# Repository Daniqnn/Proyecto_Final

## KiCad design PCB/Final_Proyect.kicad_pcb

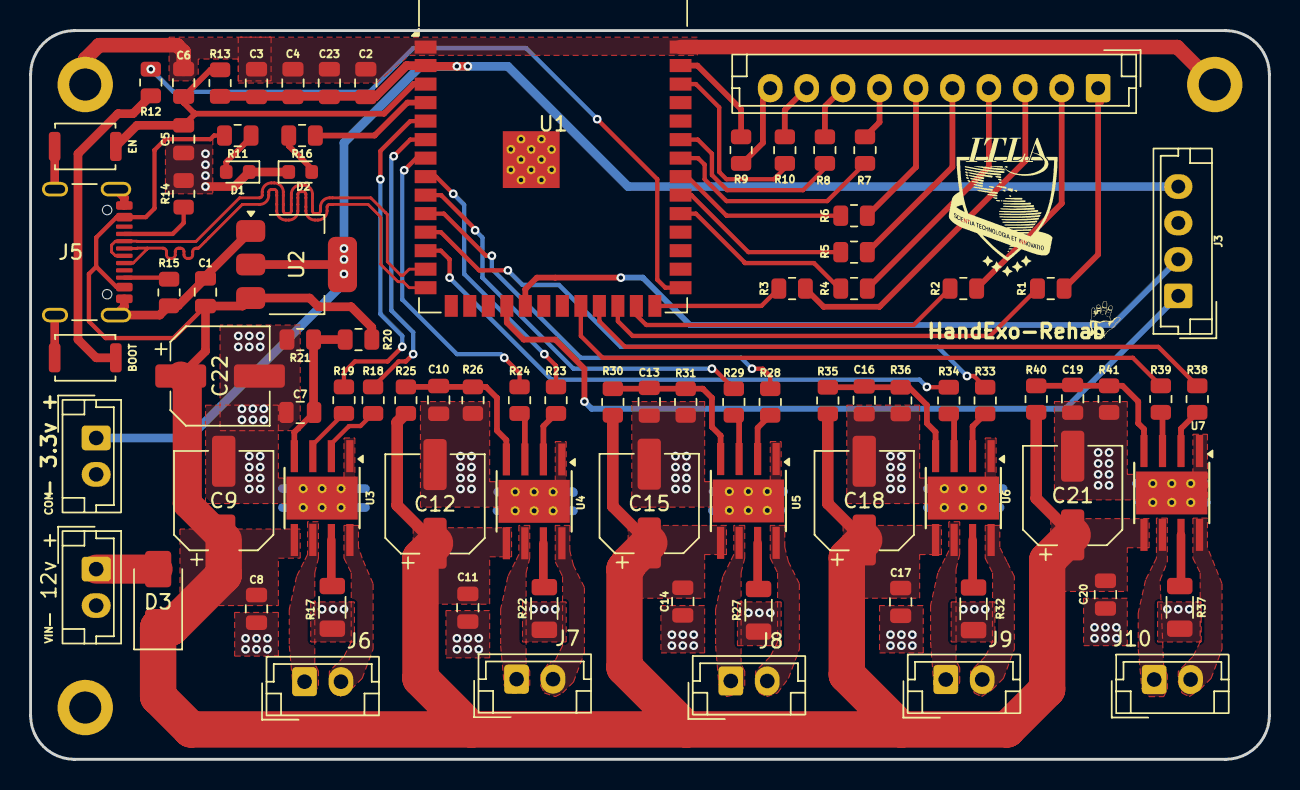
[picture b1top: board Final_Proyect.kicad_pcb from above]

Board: 2 copper layers, 85.0 x 50.0 mm, 86 parts (0 on the bottom side), 76 nets.

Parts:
- 3.3v +: VCC GND TTP223; JST_EH_B2B-EH-A_1x02_P2.50mm_Vertical
- 12v +: - +; JST_EH_B2B-EH-A_1x02_P2.50mm_Vertical
BOOT: SW_SPST; SW_Push_SPST_NO_Alps_SKRK
C1: 10uf; C_0805_2012Metric
C2, C4: 22uf; C_0805_2012Metric
C3, C6, C23: 100nf; C_0805_2012Metric
C5: 1uf; C_0805_2012Metric
C7, C8, C10, C11, C13, C14, C16, C17, C19, C20: 100nF; C_0805_2012Metric
C9, C12, C15, C18, C21: 47uF; CP_Elec_6.3x7.7
C22: 220uF; CP_Elec_6.3x7.7
D1, D2: LED; LED_0603_1608Metric
D3: SS18; D_SMA
EN: SW_SPST; SW_Push_SPST_NO_Alps_SKRK
J1: Conn_01x10_Pin; JST_EH_B10B-EH-A_1x10_P2.50mm_Vertical
J3: OLLED I2C; JST_EH_B4B-EH-A_1x04_P2.50mm_Vertical
J5: USB_C; USB_C_Receptacle_GCT_USB4105-xx-A_16P_TopMnt_Horizontal
J6, J7, J8, J9, J10: JST_EH_B2B-EH-A_1x02_P2.50mm_Vertical
R1, R2, R3, R4, R5, R6, R7, R8, R9, R10, R11, R18, R19, R23, R24, R28, R29, R33, R34, R38, R39: 1k; R_0805_2012Metric
R12: 100R; R_0805_2012Metric
R13, R21, R26, R31, R36, R41: 10k; R_0805_2012Metric
R14, R15: 5.1k; R_0805_2012Metric
R16: 330; R_0805_2012Metric
R17, R22, R27, R32, R37: 0.2; R_1206_3216Metric
R20, R25, R30, R35, R40: 80k; R_0805_2012Metric
U1: ESP32-S3-WROOM-1
U2: AMS1117-3.3; SOT-223-3_TabPin2
U3, U4, U5, U6, U7: DRV8870DDA; Texas_HTSOP-8-1EP_3.9x4.9mm_P1.27mm_EP2.95x4.9mm_Mask2.4x3.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

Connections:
+3V3: - 3.3v +.1, C2.1, C3.1, C4.1, C23.1, J3.4, R13.1, U1.2 (3V3), U2.2 (VO)
+12V: C1.1, C8.1, C9.1, C11.1, C12.1, C14.1, C15.1, C17.1, C18.1, C20.1, C21.1, C22.1, D3.1 (K), J5.A4 (VBUS), J5.A9 (VBUS), J5.B4 (VBUS), J5.B9 (VBUS), R11.2, R20.1, R25.1, R30.1, R35.1, R40.1, U2.3 (VI), U3.5 (VM), U4.5 (VM), U5.5 (VM), U6.5 (VM), U7.5 (VM)
/Motor Driver1/IN1: R24.1, U4.3 (IN1)
/Motor Driver1/IN2: R23.2, U4.2 (IN2)
/Motor Driver1/ISEN: R22.1, U4.7 (ISEN)
/Motor Driver1/M1: J7.1, U4.6 (OUT1)
/Motor Driver1/M2: J7.2, U4.8 (OUT2)
/Motor Driver1/VREF: C10.1, R25.2, R26.1, U4.4 (VREF)
/Motor Driver2/IN1: R29.1, U5.3 (IN1)
/Motor Driver2/IN2: R28.2, U5.2 (IN2)
/Motor Driver2/ISEN: R27.1, U5.7 (ISEN)
/Motor Driver2/M1: J8.1, U5.6 (OUT1)
/Motor Driver2/M2: J8.2, U5.8 (OUT2)
/Motor Driver2/VREF: C13.1, R30.2, R31.1, U5.4 (VREF)
/Motor Driver3/IN1: R34.1, U6.3 (IN1)
/Motor Driver3/IN2: R33.2, U6.2 (IN2)
/Motor Driver3/ISEN: R32.1, U6.7 (ISEN)
/Motor Driver3/M1: J9.1, U6.6 (OUT1)
/Motor Driver3/M2: J9.2, U6.8 (OUT2)
/Motor Driver3/VREF: C16.1, R35.2, R36.1, U6.4 (VREF)
/Motor Driver4/IN1: R39.1, U7.3 (IN1)
/Motor Driver4/IN2: R38.2, U7.2 (IN2)
/Motor Driver4/ISEN: R37.1, U7.7 (ISEN)
/Motor Driver4/M1: J10.1, U7.6 (OUT1)
/Motor Driver4/M2: J10.2, U7.8 (OUT2)
/Motor Driver4/VREF: C19.1, R40.2, R41.1, U7.4 (VREF)
/Motor Driver/IN1: R19.1, U3.3 (IN1)
/Motor Driver/IN2: R18.2, U3.2 (IN2)
/Motor Driver/ISEN: R17.1, U3.7 (ISEN)
/Motor Driver/M1: J6.1, U3.6 (OUT1)
/Motor Driver/M2: J6.2, U3.8 (OUT2)
/Motor Driver/VREF: C7.1, R20.2, R21.1, U3.4 (VREF)
A+: R18.1, U1.6 (IO6)
A-: R19.2, U1.5 (IO5)
B+: R23.1, U1.8 (IO15)
B-: R24.2, U1.7 (IO7)
BOOT: R12.2, U1.27 (IO0)
C+: R28.1, U1.10 (IO17)
C-: R29.2, U1.9 (IO16)
D+: J5.A6 (D+), J5.B6 (D+), U1.14 (USB_D+)
D-: J5.A7 (D-), J5.B7 (D-), U1.13 (USB_D-)
E+: R33.1, U1.11 (IO18)
E-: R34.2, U1.12 (IO8)
EN: C5.1, C6.2, EN.1 (A), R13.2, U1.3 (EN)
F+: R38.1, U1.23 (IO21)
F-: R39.2, U1.22 (IO14)
GND: - 3.3v +.2, - 12v +.2, BOOT.2 (B), C1.2, C2.2, C3.2, C4.2, C5.2, C6.1, C7.2, C8.2, C9.2, C10.2, C11.2, C12.2, C13.2, C14.2, C15.2, C16.2, C17.2, C18.2, C19.2, C20.2, C21.2, C22.2, C23.2, D1.1 (K), D2.1 (K), EN.2 (B), J3.3, J5.A1 (GND), J5.A12 (GND), J5.B1 (GND), J5.B12 (GND), J5.S1 (SHIELD), R14.2, R15.2, R17.2, R21.2, R22.2, R26.2, R27.2, R31.2, R32.2, R36.2, R37.2, R41.2, U1.1 (GND), U1.40 (GND), U1.41 (GND), U2.1 (GND), U3.1 (GND), U3.9 (GND), U4.1 (GND), U4.9 (GND), U5.1 (GND), U5.9 (GND), U6.1 (GND), U6.9 (GND), U7.1 (GND), U7.9 (GND)
Led: R16.2, U1.4 (IO4)
unnamed: BOOT.1 (A), R12.1
unnamed: D1.2 (A), R11.1
unnamed: D2.2 (A), R16.1
unnamed: - 12v +.1, D3.2 (A)
unnamed: J1.1, R1.1
unnamed: J1.2, R2.1
unnamed: J1.3, R3.1
unnamed: J1.4, R4.1
unnamed: J1.5, R5.1
unnamed: J1.6, R6.1
unnamed: J1.7, R7.1
unnamed: J1.8, R8.1
unnamed: J1.9, R10.1
unnamed: J1.10, R9.1
unnamed: J5.A5 (CC1), R14.1
unnamed: J5.B5 (CC2), R15.1
SCL: J3.2, U1.19 (IO11)
SDA: J3.1, U1.18 (IO10)
SIG1: R10.2, U1.38 (IO2)
SIG2: R9.2, U1.39 (IO1)
SIG3: R8.2, U1.35 (IO42)
SIG4: R7.2, U1.34 (IO41)
SIG5: R6.2, U1.33 (IO40)
SIG6: R5.2, U1.32 (IO39)
SIG7: R4.2, U1.31 (IO38)
SIG8: R3.2, U1.26 (IO45)
SIG9: R2.2, U1.25 (IO48)
SIG10: R1.2, U1.24 (IO47)

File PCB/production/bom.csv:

Designator,Footprint,Quantity,Value,LCSC Part #
"_2, ",,2,,
"BOOT, EN",SW_Push_SPST_NO_Alps_SKRK,2,SW_SPST,C49234124
C1,0805,1,10uf,C15850
"C10, C11, C13, C14, C16, C17, C19, C20, C3, C6, C7, C8",0805,12,100nF,C519981
"C12, C15, C18, C21, C9",CP_Elec_6.3x7.7,5,47uF,C7469965
"C2, C4",0805,2,22uf,C602037
C22,CP_Elec_6.3x7.7,1,220uF,C7469965
C23,0805,1,100nf,C602037
C5,0805,1,1uf,C116352
D1,0603,1,LED,C965799
D2,0603,1,LED,C965807
D3,D_SMA,1,SS18,
J5,USB_C_Receptacle_GCT_USB4105-xx-A_16P_TopMnt_Horizontal,1,USB_C,C2988369
"R1, R10, R11, R18, R19, R2, R23, R24, R28, R29, R3, R33, R34, R38, R39, R4, R5, R6, R7, R8, R9",0805,21,1k,C2907232
R12,0805,1,100R,C17408
"R13, R21, R26, R31, R36, R41",0805,6,10k,
"R14, R15",0805,2,5.1k,C27834
R16,0805,1,330,C2930157
"R17, R22, R27, R32, R37",1206,5,0.2,C44051
"R20, R25, R30, R35, R40",0805,5,80k,C2960781
U1,ESP32-S3-WROOM-1,1,ESP32-S3-WROOM-1,C2913198
U2,SOT-223-3_TabPin2,1,AMS1117-3.3,C347222
"U3, U4, U5, U6, U7",Texas_HTSOP-8-1EP_3.9x4.9mm_P1.27mm_EP2.95x4.9mm_Mask2.4x3.1mm_ThermalVias,5,DRV8870DDA,C86590

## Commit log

2026-02-07 Actualizacion 7/2/26
2026-02-08 Actualizacion diseño PCB
2026-02-08 Actualizacion de Drivers
2026-02-09 Version enrutada
2026-02-09 version enrutada 1.0
2026-02-20 Enrutamiento mejorado
2026-03-03 Finalizado
2026-04-10 Actualizacion Codigo
2026-04-14 Actualizacion de codigo
2026-04-19 Actualizacion Codigo (Control de velocidad)
2026-04-23 22/04/2026 Finalizado
2026-05-06 Diseños
